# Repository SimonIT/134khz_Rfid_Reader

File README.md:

# 134.2 kHz RFID Reader (EM4095 + ESP32)

A low-frequency RFID reader designed and built to explore the fundamentals of LF RFID communication systems at 134.2 kHz.

This project uses the EM4095 RFID analog front-end with an ESP32 for signal processing and data handling. A custom PCB with an integrated coil antenna was designed specifically for this implementation.

---

## Overview

The system operates at 134.2 kHz and detects compatible LF RFID tags through magnetic field coupling. The EM4095 handles signal amplification and demodulation, while the ESP32 processes the received data.

The project was developed as a practical hardware learning experience covering:
- RFID communication principles
- Analog front-end interfacing
- Coil antenna design
- PCB design and testing
- Embedded firmware development

---

## Features

- 134.2 kHz low-frequency RFID operation
- Custom-designed PCB
- Integrated PCB coil antenna
- EM4095 RFID analog front-end
- ESP32-based data processing
- Compact hardware design

---

## System Architecture

1. The PCB coil antenna generates a magnetic field at 134.2 kHz.
2. When an RFID tag enters the field, the tag modulates the carrier signal.
3. The EM4095 detects and demodulates the received signal.
4. The ESP32 reads and processes the decoded data.

---

## Project Images

### PCB Layout

### 3D View

### Schematic

---

## Hardware Components

- EM4095 RFID IC
- ESP32
- Custom PCB coil antenna

---

## Repository Structure

```text
hardware/   -> PCB layout and schematic files
software/   -> ESP32 firmware
images/     -> Project images

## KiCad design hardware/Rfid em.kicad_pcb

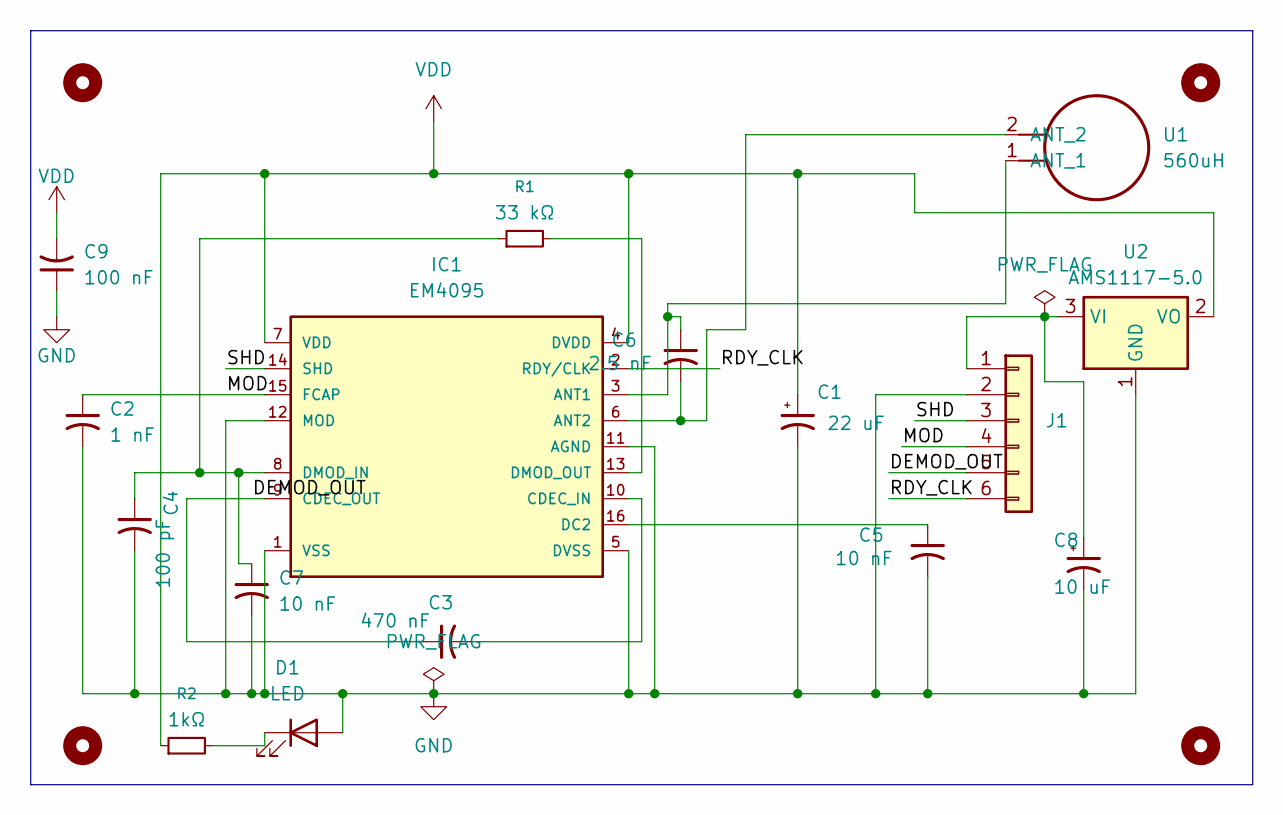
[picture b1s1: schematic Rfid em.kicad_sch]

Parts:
C1: 22 uF; CP_EIA-3528-21_Kemet-B; MPN T491B226K016AT
C2: 1 nF; C_0805_2012Metric
C3: 470 nF; C_0805_2012Metric
C4: 100 pF; C_0805_2012Metric
C5, C7: 10 nF; C_0805_2012Metric
C6: 2.5 nF; C_0805_2012Metric
C8: 10 uF; CP_EIA-3216-18_Kemet-A; MPN T491A106K016AT
C9: 100 nF; C_0805_2012Metric; MPN GRM21BR71H104KA01L
D1: LED; LED_1206_3216Metric
H1, H2, H3, H4: MountingHole; MountingHole_3.5mm
IC1: EM4095; SOIC-16_3.9x9.9mm_P1.27mm
J1: Conn_01x06; PinHeader_1x06_P2.54mm_Vertical
R1: 33 kΩ; R_0805_2012Metric
R2: 1kΩ; R_1206_3216Metric
U1: 560uH; RFID_COIL
U2: AMS1117-5.0; SOT-223-3_TabPin2

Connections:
/DEMOD_OUT: C3.1, IC1.9 (CDEC_OUT), J1.5
/MOD: C2.1, IC1.15 (FCAP), J1.4
/RDY_CLK: IC1.2 (RDY/CLK), J1.6
/SHD: IC1.14 (SHD), J1.3
GND: C1.2, C2.2, C4.2, C5.2, C7.2, C8.2, C9.1, D1.2 (A), IC1.1 (VSS), IC1.5 (DVSS), IC1.11 (AGND), IC1.12 (MOD), J1.2, U2.1 (GND)
unnamed: D1.1 (K), R2.2
unnamed: C6.1, IC1.3 (ANT1), U1.1 (ANT_1)
unnamed: C6.2, IC1.6 (ANT2), U1.2 (ANT_2)
unnamed: C3.2, IC1.10 (CDEC_IN)
unnamed: C5.1, IC1.16 (DC2)
unnamed: C4.1, C7.1, IC1.8 (DMOD_IN), R1.1
unnamed: IC1.13 (DMOD_OUT), R1.2
unnamed: C8.1, J1.1, U2.3 (VI)
VDD: C1.1, C9.2, IC1.4 (DVDD), IC1.7 (VDD), R2.1, U2.2 (VO)

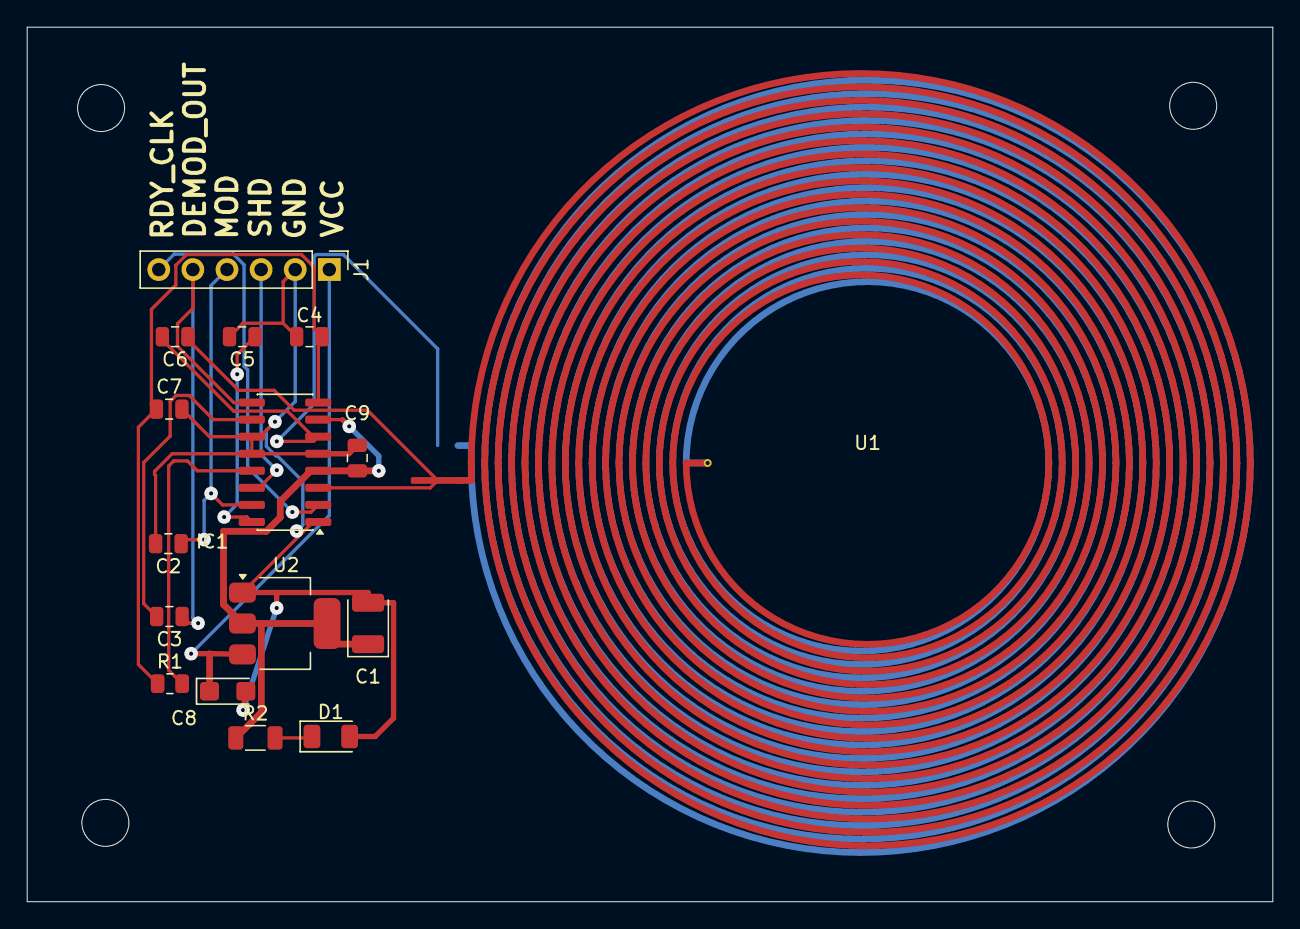
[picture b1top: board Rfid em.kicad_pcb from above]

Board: 2 copper layers, 92.7 x 65.1 mm, 20 parts (0 on the bottom side), 14 nets.

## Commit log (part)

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2026-05-10 Revise README for improved clarity and organization
    Updated README to enhance clarity and structure, including sections on features, system architecture, and hardware components.
